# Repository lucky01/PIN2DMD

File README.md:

# PIN2DMD - a color LED dotmatrix controller for virtual and real pinballs

With the PIN2DMD project you get a full color LED DMD controller 
for real and virtual pinball machines.
The project was started by Lucky1 and shortly after that joined by Steve45 
as co-author. Version 1.X is free for DIY private NON COMMERCIAL use and released under 
a Creative Commons Attribution-NonCommercial- ShareAlike 4.0 International License.

http://creativecommons.org/licenses/by-nc-sa/4.0/

Due to copyright violations through commercial sales of our software the authors were forced to
change the project to allow access to the source code for contributors only with version 2.0.
Also a activation key which is bound to the hardware was introduced.
More Information how to obtain a key can be found in chapter 3 here https://pin2dmd.com/installation/ 

The latest binary can be found here 
https://github.com/lucky01/PIN2DMD/raw/master/firmware/latest/

Sorry for inconvinience, but is seems that the hunt for quick money eats the brain of the hunter.

More information can be found on https://pin2dmd.com/

It currently supports:

- WPC/WPC95 real pinball input
- Stern SAM real pinball input
- Stern Whitestar real pinball input
- Stern Spike real pinball input
- DataEast/Sega real pinball input
- Gottlieb real pinball input
- Capcom real pinball input
- AlvinG real pinball input
- Spooky real pinball input (with full color support from herg for AMH http://ledocd.com/amh_color/)
- Inder / SPinball real pinball input
- Sleic / Petaco real pinball input
- HomePin real pinball input
- Sega 192x64 using 64x64 1/32scan P2 Panels
- DataEast 128x16 real pinball input
- Mission Pinball Factory and P-ROC USB input
- Visual Pinball / PinMame USB input
- Future Pinball with DMD interceptor DLL
- Unit3d Pinball
- Ultra DMD support (Stephen)
- PinballX / XDMD support (Tom Speirs)
- Pinball fx2 support using dmdext from Freezy
- The Pinball Arcade support using dmdext from Freezy and NoEx
- Pinball Browser / SmartDMD color switching for full color Stern ROMS
- Frame colorization with PIN2DMD Editor by Steve for all pinball machines
- WCID Windows automated driver installation

The components cost approximately 120$
Here is a list of what you need:
 
#1. The Panels
The panels we use are sold for video walls and advertising signs. There are many 
sizes of panels available with different spacing between the LEDs. The ones 
that fit best into a pinball have 2.5mm spacing (also referred to as P2.5), 
which results in a 128×32 display of 320×76.8mm. This can be mounted into an 
existing DMD/speaker panel from a pinball cabinet. Currently the only place 
to buy these panels is from AliExpress. search for "RGB LED 64x64 p2.5 1/16" or 
"RGB LED 64x64 p2.5 1/16". You don´t find 128×32 panels, but you can buy two 
64×32 or one 64x64 panel which consists of two 64x32 panels which can be removed 
from the frame and connect side-by-side. Make sure that you end up with 2 x 1/16 
scan panels since these are the only one currently supported by PIN2DMD. 
The good thing is that they are seamless.

#2. The Controller

#2.1 The STM32 Nucleo board with PIN2DMD Shield or EVO boards

The panels use a 16 pin Hub75 interface to be connected to the next panel or to a 
controller. We use standard STM32 development boards like the Nucleo144-F429ZI or NUCLEO-F439ZI
which are available from multiple sources for about $20 or custom EVO boards.
The proceesor is based on a ARM Cortex processor architecture which is needed 
for the rapid bit-shifting of data to control the panels. We write the program in C/C++. 
The software is uploaded to the controller through USB port.
To connect the displays to the controller there is a HUB75 connector, which 
basically just connects the pins to the 16-pin ribbon cable that drives the displays. 
The board also has a 14pin connector which is used as input to get the data from a real machine. 
PCB layout examples can be found in the hardware directory. 

#3. The Power Supply
The RGB LED displays require 5vdc for power and if you want to run them
with full brightness they need a lot of current. A 10A power should be enough.
You need to connect that power supply up to both panels. The controller can 
either be supplied by USB or by an external 5V power source
 
#4. The Firmware
Installation is done using ST-Link interface

1) Download and install ST Link Utility: http://www.st.com/web/en/catalog/tools/PF258168
2) The latest binary can be found here https://github.com/lucky01/PIN2DMD/raw/master/firmware/latest/
3) Connect the STM32 board to the PC using a mini-USB cable (not the smaller microUSB cable). The board will light up and you should an STM32 STLink USB device connected in the Windows notification tray
4) Flash firmware: Target -> Program 
Choose PIN2DMD.BIN file from firmware/latest latest folder.

#5. The pin2dmd.exe tool
The tool is used to configure the controller und upload needed data for the pinball
used. It can either run in commandline mode or in GUI mode.

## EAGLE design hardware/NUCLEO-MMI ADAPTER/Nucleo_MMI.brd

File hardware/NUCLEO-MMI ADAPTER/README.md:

# PIN2DMD Nucleo MMI adapter

The files are provided as is for unmodified production use only.
Any modification without written approval is forbidden.

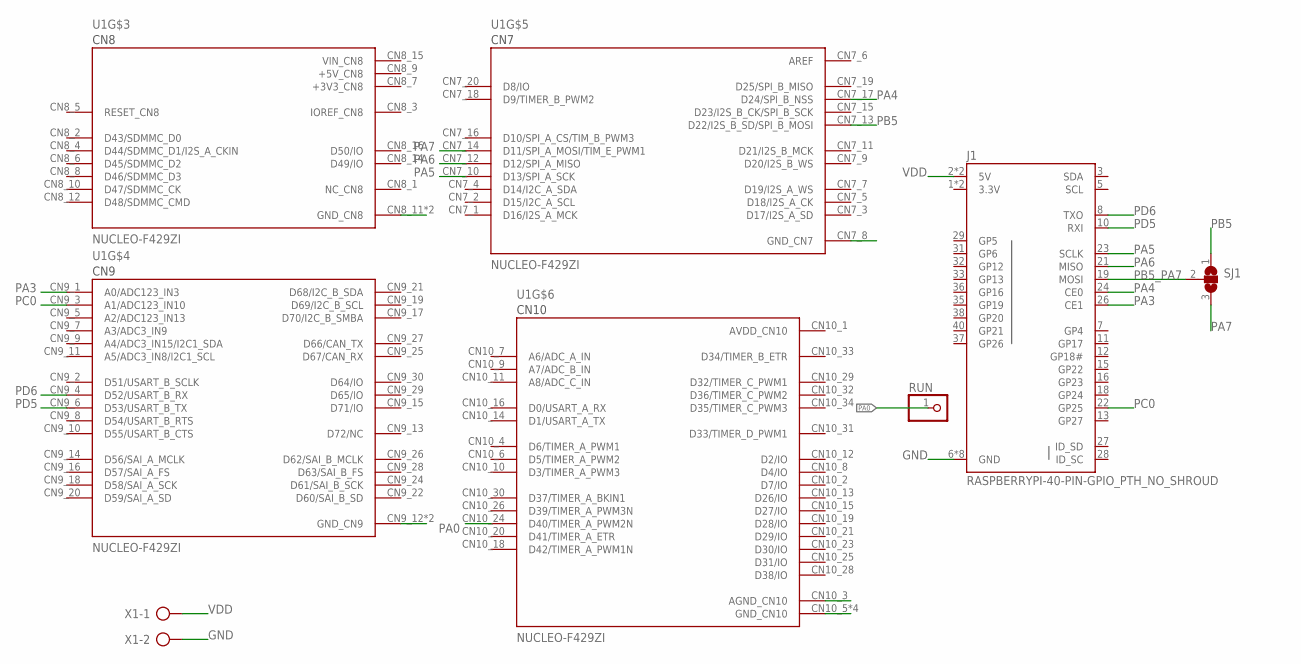
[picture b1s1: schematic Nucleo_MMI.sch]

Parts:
J1: RASPBERRYPI-40-PIN-GPIO_PTH_NO_SHROUD; 2X20
RUN: PINHD-1X1; 1X01
SJ1: SJ2W; SJ_2
U1: NUCLEO-F429ZI; MODULE_NUCLEO-F429ZI
X1: AK500/2-H

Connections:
3.3V: J1.1 (3.3V), J1.17 (3.3V)
+3V3_CN8: U1.CN8_7 (+3V3_CN8)
+5V_CN8: U1.CN8_9 (+5V_CN8)
AREF: U1.CN7_6 (AREF)
AVDD_CN10: U1.CN10_1 (AVDD_CN10)
GND: J1.6 (GND), J1.9 (GND), J1.14 (GND), J1.20 (GND), J1.25 (GND), J1.30 (GND), J1.34 (GND), J1.39 (GND), U1.CN7_8 (GND_CN7), U1.CN8_11 (GND_CN8), U1.CN8_13 (GND_CN8), U1.CN9_12 (GND_CN9), U1.CN9_23 (GND_CN9), U1.CN10_3 (AGND_CN10), U1.CN10_5 (GND_CN10), U1.CN10_17 (GND_CN10), U1.CN10_22 (GND_CN10), U1.CN10_27 (GND_CN10), X1.2
PA0: RUN.1, U1.CN10_24 (D40/TIMER_A_PWM2N)
PA3: J1.26 (CE1), U1.CN9_1 (A0/ADC123_IN3)
PA4: J1.24 (CE0), U1.CN7_17 (D24/SPI_B_NSS)
PA5: J1.23 (SCLK), U1.CN7_10 (D13/SPI_A_SCK)
PA6: J1.21 (MISO), U1.CN7_12 (D12/SPI_A_MISO)
PA7: SJ1.3, U1.CN7_14 (D11/SPI_A_MOSI/TIM_E_PWM1)
PB5: SJ1.1, U1.CN7_13 (D22/I2S_B_SD/SPI_B_MOSI)
PB5_PA7: J1.19 (MOSI), SJ1.2
PC0: J1.22 (GP25), U1.CN9_3 (A1/ADC123_IN10)
PD5: J1.10 (RXI), U1.CN9_6 (D53/USART_B_TX)
PD6: J1.8 (TXO), U1.CN9_4 (D52/USART_B_RX)
VDD: J1.2 (5V), J1.4 (5V), X1.1
VIN_CN8: U1.CN8_15 (VIN_CN8)

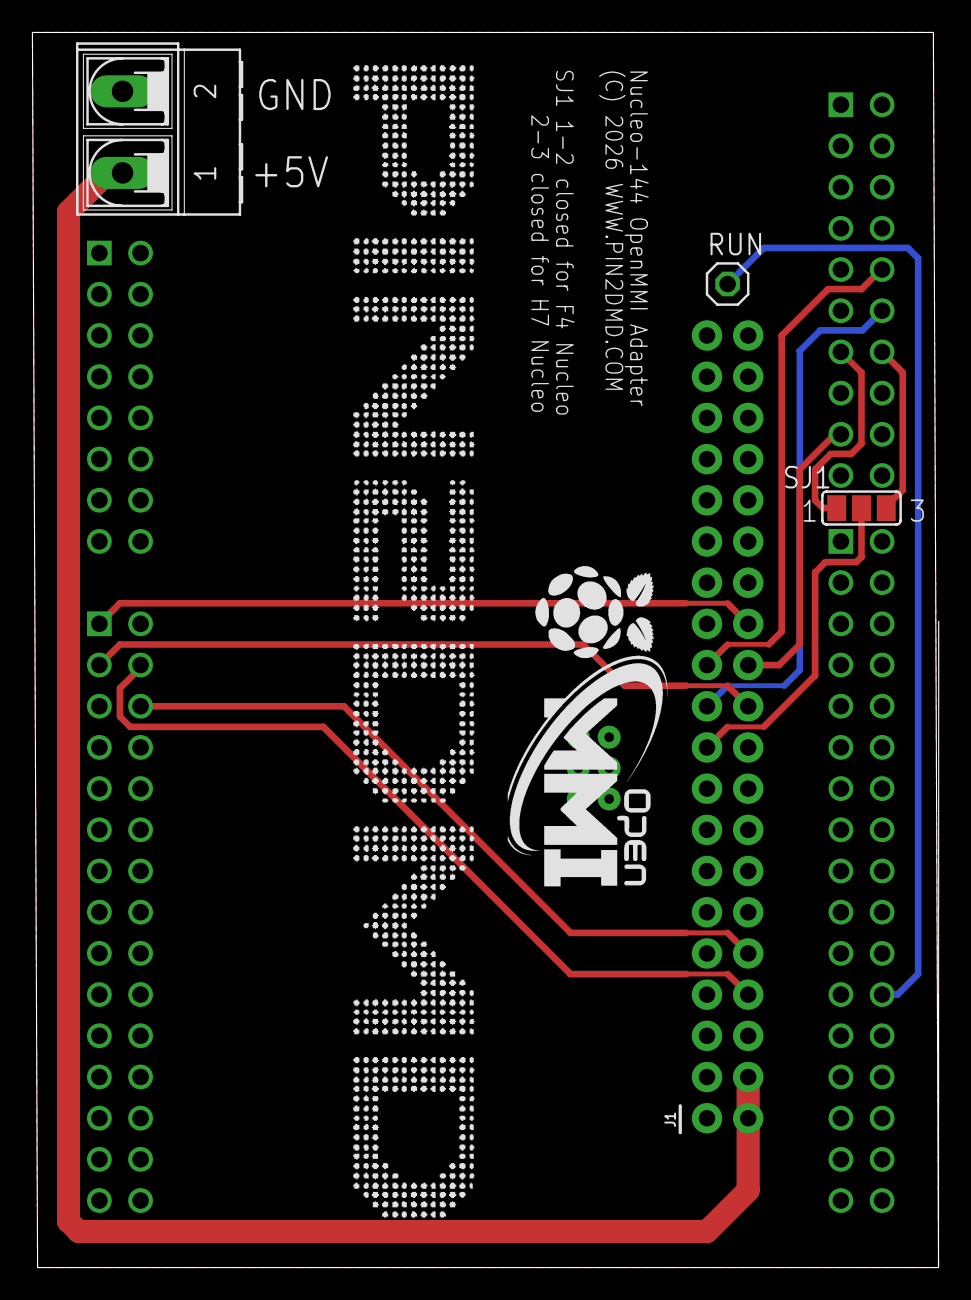
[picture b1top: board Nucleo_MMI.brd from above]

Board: 2 copper layers, 55.9 x 76.2 mm, 5 parts (1 on the bottom side), 14 nets.

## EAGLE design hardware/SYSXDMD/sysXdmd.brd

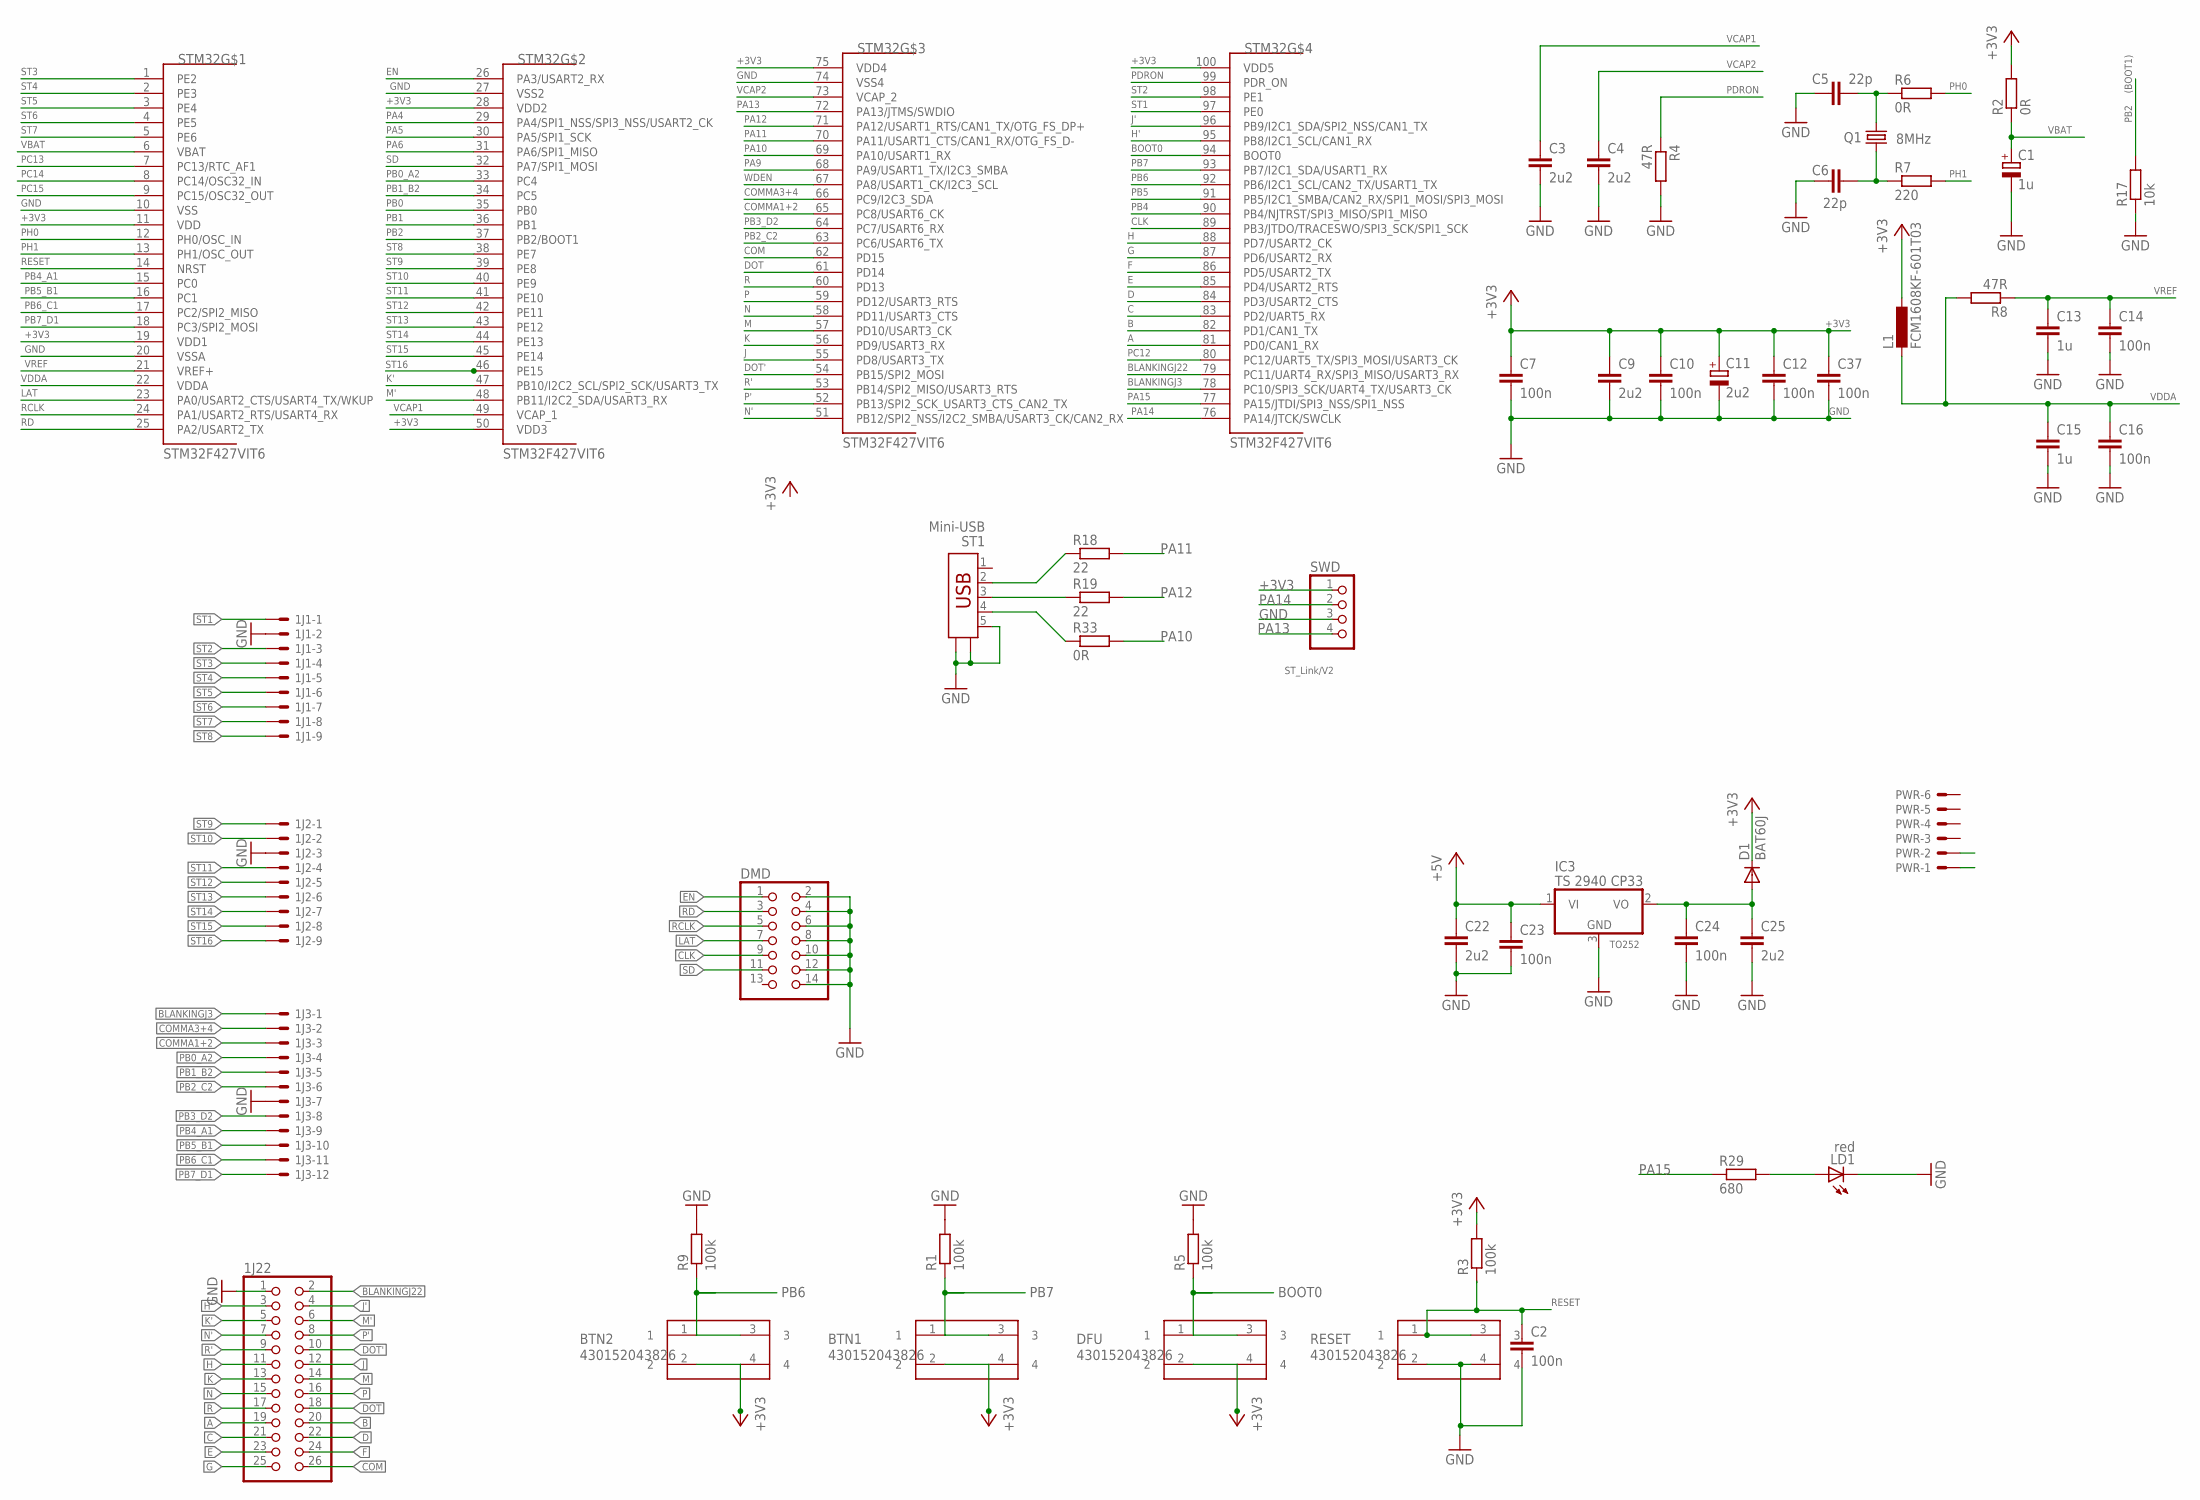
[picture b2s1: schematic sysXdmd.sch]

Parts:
1J1, 1J2: KK-156-9
1J3: KK-156-12
1J22: PINHD-2X13; 2X13
BTN1, BTN2: 430152043826
C1: 1u; CT3528
C2, C7, C10, C12, C14, C16, C23, C24, C37: 100n; C0805
C3, C4: 2u2; C0805
C5, C6: 22p; C0805
C9, C22, C25: 2u2; C1206
C11: 2u2; CT3528
C13, C15: 1u; C1206
D1: BAT60J; SOD323-W
DFU: 430152043826
DMD: PINHD-2X7; 2X07
IC3: TS 2940 CP33; TO252
L1: FCM1608KF-601T03; L0603
LD1: red; CHIP-LED0805
PWR: KK-156-6
Q1: 8MHz; HC49UP
R1, R3, R5, R9: 100k; R0805
R2, R6, R33: 0R; R0805
R4, R8: 47R; R0805
R7: 220; R0805
R17: 10k; R0805
R18, R19: 22; R0805
R29: 680; R0805
RESET: 430152043826
ST1: Mini-USB; USBMINI
STM32: STM32F427VIT6; LQFP100
SWD: PINHD-1X4; 1X04

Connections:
+3V3: BTN1.2, BTN1.4, BTN2.2, BTN2.4, C7.1, C9.1, C10.1, C11.+, C12.1, C37.1, D1.C, DFU.2, DFU.4, L1.1, R2.2, R3.2, STM32.11 (VDD), STM32.19 (VDD1), STM32.28 (VDD2), STM32.50 (VDD3), STM32.75 (VDD4), STM32.100 (VDD5), SWD.1
+5V: C22.1, C23.1, IC3.1 (VI), PWR.1
A: 1J22.19, STM32.81 (PD0/CAN1_RX)
B: 1J22.20, STM32.82 (PD1/CAN1_TX)
BLANKINGJ3: 1J3.1, STM32.78 (PC10/SPI3_SCK/UART4_TX/USART3_CK)
BLANKINGJ22: 1J22.2, STM32.79 (PC11/UART4_RX/SPI3_MISO/USART3_RX)
BOOT0: DFU.1, DFU.3, R5.1, STM32.94 (BOOT0)
C: 1J22.21, STM32.83 (PD2/UART5_RX)
CLK: DMD.9, STM32.89 (PB3/JTDO/TRACESWO/SPI3_SCK/SPI1_SCK)
COM: 1J22.26, STM32.62 (PD15)
COMMA1+2: 1J3.3, STM32.65 (PC8/USART6_CK)
COMMA3+4: 1J3.2, STM32.66 (PC9/I2C3_SDA)
D: 1J22.22, STM32.84 (PD3/USART2_CTS)
DOT: 1J22.18, STM32.61 (PD14)
DOT': 1J22.10, STM32.54 (PB15/SPI2_MOSI)
E: 1J22.23, STM32.85 (PD4/USART2_RTS)
EN: DMD.1, STM32.26 (PA3/USART2_RX)
F: 1J22.24, STM32.86 (PD5/USART2_TX)
G: 1J22.25, STM32.87 (PD6/USART2_RX)
GND: 1J1.2, 1J2.3, 1J3.7, 1J22.1, C1.-, C2.2, C3.2, C4.2, C5.2, C6.2, C7.2, C9.2, C10.2, C11.-, C12.2, C13.2, C14.2, C15.2, C16.2, C22.2, C23.2, C24.2, C25.2, C37.2, DMD.2, DMD.4, DMD.6, DMD.8, DMD.10, DMD.12, DMD.14, IC3.3 (GND), LD1.C, PWR.2, R1.2, R4.2, R5.2, R9.2, R17.1, RESET.2, RESET.4, ST1.5, ST1.N1, ST1.N2, STM32.10 (VSS), STM32.20 (VSSA), STM32.27 (VSS2), STM32.74 (VSS4), SWD.3
H: 1J22.11, STM32.88 (PD7/USART2_CK)
H': 1J22.3, STM32.95 (PB8/I2C1_SCL/CAN1_RX)
J: 1J22.12, STM32.55 (PD8/USART3_TX)
J': 1J22.4, STM32.96 (PB9/I2C1_SDA/SPI2_NSS/CAN1_TX)
K: 1J22.13, STM32.56 (PD9/USART3_RX)
K': 1J22.5, STM32.47 (PB10/I2C2_SCL/SPI2_SCK/USART3_TX)
LAT: DMD.7, STM32.23 (PA0/USART2_CTS/USART4_TX/WKUP)
M: 1J22.14, STM32.57 (PD10/USART3_CK)
M': 1J22.6, STM32.48 (PB11/I2C2_SDA/USART3_RX)
N: 1J22.15, STM32.58 (PD11/USART3_CTS)
unnamed: C5.1, Q1.2, R6.1
unnamed: C6.1, Q1.1, R7.1
unnamed: C24.1, C25.1, D1.A, IC3.2 (VO)
unnamed: LD1.A, R29.2
unnamed: R33.1, ST1.4
unnamed: R19.1, ST1.3
unnamed: R18.1, ST1.2
N': 1J22.7, STM32.51 (PB12/SPI2_NSS/I2C2_SMBA/USART3_CK/CAN2_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)
P: 1J22.16, STM32.59 (PD12/USART3_RTS)
P': 1J22.8, STM32.52 (PB13/SPI2_SCK_USART3_CTS_CAN2_TX)
PA4: STM32.29 (PA4/SPI1_NSS/SPI3_NSS/USART2_CK)
PA5: STM32.30 (PA5/SPI1_SCK)
PA6: STM32.31 (PA6/SPI1_MISO)
PA9: STM32.68 (PA9/USART1_TX/I2C3_SMBA)
PA10: R33.2, STM32.69 (PA10/USART1_RX)
PA11: R18.2, STM32.70 (PA11/USART1_CTS/CAN1_RX/OTG_FS_D-)
PA12: R19.2, STM32.71 (PA12/USART1_RTS/CAN1_TX/OTG_FS_DP+)
PA13: STM32.72 (PA13/JTMS/SWDIO), SWD.4
PA14: STM32.76 (PA14/JTCK/SWCLK), SWD.2
PA15: R29.1, STM32.77 (PA15/JTDI/SPI3_NSS/SPI1_NSS)
PB0: STM32.35 (PB0)
PB0_A2: 1J3.4, STM32.33 (PC4)
PB1: STM32.36 (PB1)
PB1_B2: 1J3.5, STM32.34 (PC5)
PB2: R17.2, STM32.37 (PB2/BOOT1)
PB2_C2: 1J3.6, STM32.63 (PC6/USART6_TX)
PB3_D2: 1J3.8, STM32.64 (PC7/USART6_RX)
PB4: STM32.90 (PB4/NJTRST/SPI3_MISO/SPI1_MISO)
PB4_A1: 1J3.9, STM32.15 (PC0)
PB5: STM32.91 (PB5/I2C1_SMBA/CAN2_RX/SPI1_MOSI/SPI3_MO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)
PB5_B1: 1J3.10, STM32.16 (PC1)
PB6: BTN2.1, BTN2.3, R9.1, STM32.92 (PB6/I2C1_SCL/CAN2_TX/USART1_TX)
PB6_C1: 1J3.11, STM32.17 (PC2/SPI2_MISO)
PB7: BTN1.1, BTN1.3, R1.1, STM32.93 (PB7/I2C1_SDA/USART1_RX)
PB7_D1: 1J3.12, STM32.18 (PC3/SPI2_MOSI)
PC12: STM32.80 (PC12/UART5_TX/SPI3_MOSI/USART3_CK)
PC13: STM32.7 (PC13/RTC_AF1)
PC14: STM32.8 (PC14/OSC32_IN)
PC15: STM32.9 (PC15/OSC32_OUT)
PDRON: R4.1, STM32.99 (PDR_ON)
PH0: R6.2, STM32.12 (PH0/OSC_IN)
PH1: R7.2, STM32.13 (PH1/OSC_OUT)
R: 1J22.17, STM32.60 (PD13)
R': 1J22.9, STM32.53 (PB14/SPI2_MISO/USART3_RTS)
RCLK: DMD.5, STM32.24 (PA1/USART2_RTS/USART4_RX)
RD: DMD.3, STM32.25 (PA2/USART2_TX)
RESET: C2.1, R3.1, RESET.1, RESET.3, STM32.14 (NRST)
SD: DMD.11, STM32.32 (PA7/SPI1_MOSI)
ST1: 1J1.1, STM32.97 (PE0)
ST2: 1J1.3, STM32.98 (PE1)
ST3: 1J1.4, STM32.1 (PE2)
ST4: 1J1.5, STM32.2 (PE3)
ST5: 1J1.6, STM32.3 (PE4)
ST6: 1J1.7, STM32.4 (PE5)
ST7: 1J1.8, STM32.5 (PE6)
ST8: 1J1.9, STM32.38 (PE7)
ST9: 1J2.1, STM32.39 (PE8)
ST10: 1J2.2, STM32.40 (PE9)
ST11: 1J2.4, STM32.41 (PE10)
ST12: 1J2.5, STM32.42 (PE11)
ST13: 1J2.6, STM32.43 (PE12)
ST14: 1J2.7, STM32.44 (PE13)
ST15: 1J2.8, STM32.45 (PE14)
ST16: 1J2.9, STM32.46 (PE15)
VBAT: C1.+, R2.1, STM32.6 (VBAT)
VCAP1: C3.1, STM32.49 (VCAP_1)
VCAP2: C4.1, STM32.73 (VCAP_2)
VDDA: C15.1, C16.1, L1.2, R8.2, STM32.22 (VDDA)
VREF: C13.1, C14.1, R8.1, STM32.21 (VREF+)
WDEN: STM32.67 (PA8/USART1_CK/I2C3_SCL)

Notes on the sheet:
TO252
(BOOT1)
ST_Link/V2

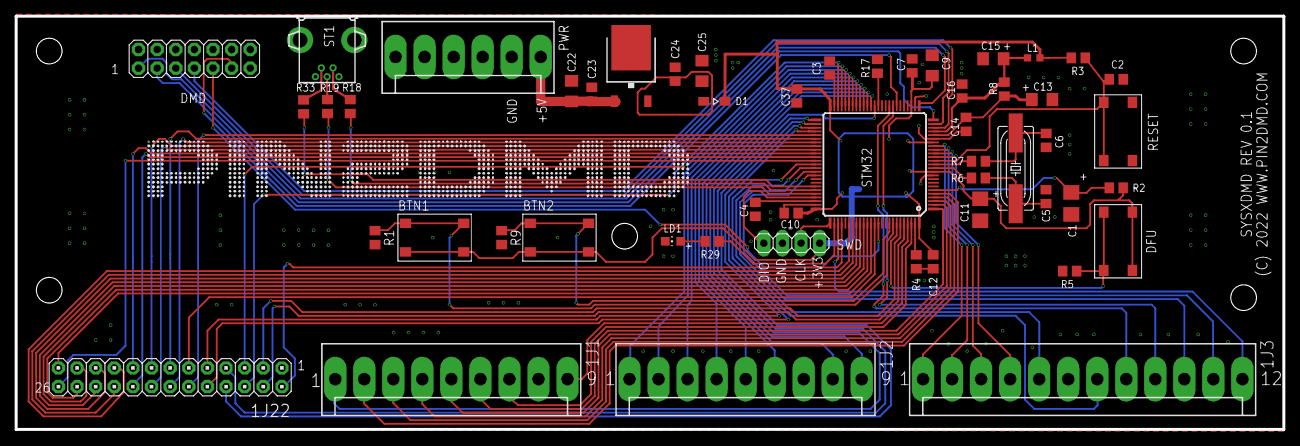
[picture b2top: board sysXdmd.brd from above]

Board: 2 copper layers, 172.9 x 56.4 mm, 52 parts (0 on the bottom side), 87 nets.

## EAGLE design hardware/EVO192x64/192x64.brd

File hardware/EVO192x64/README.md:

# PIN2DMD EVO192x64

The files are provided as is for unmodified production use only.
Any modification without written approval is forbidden.

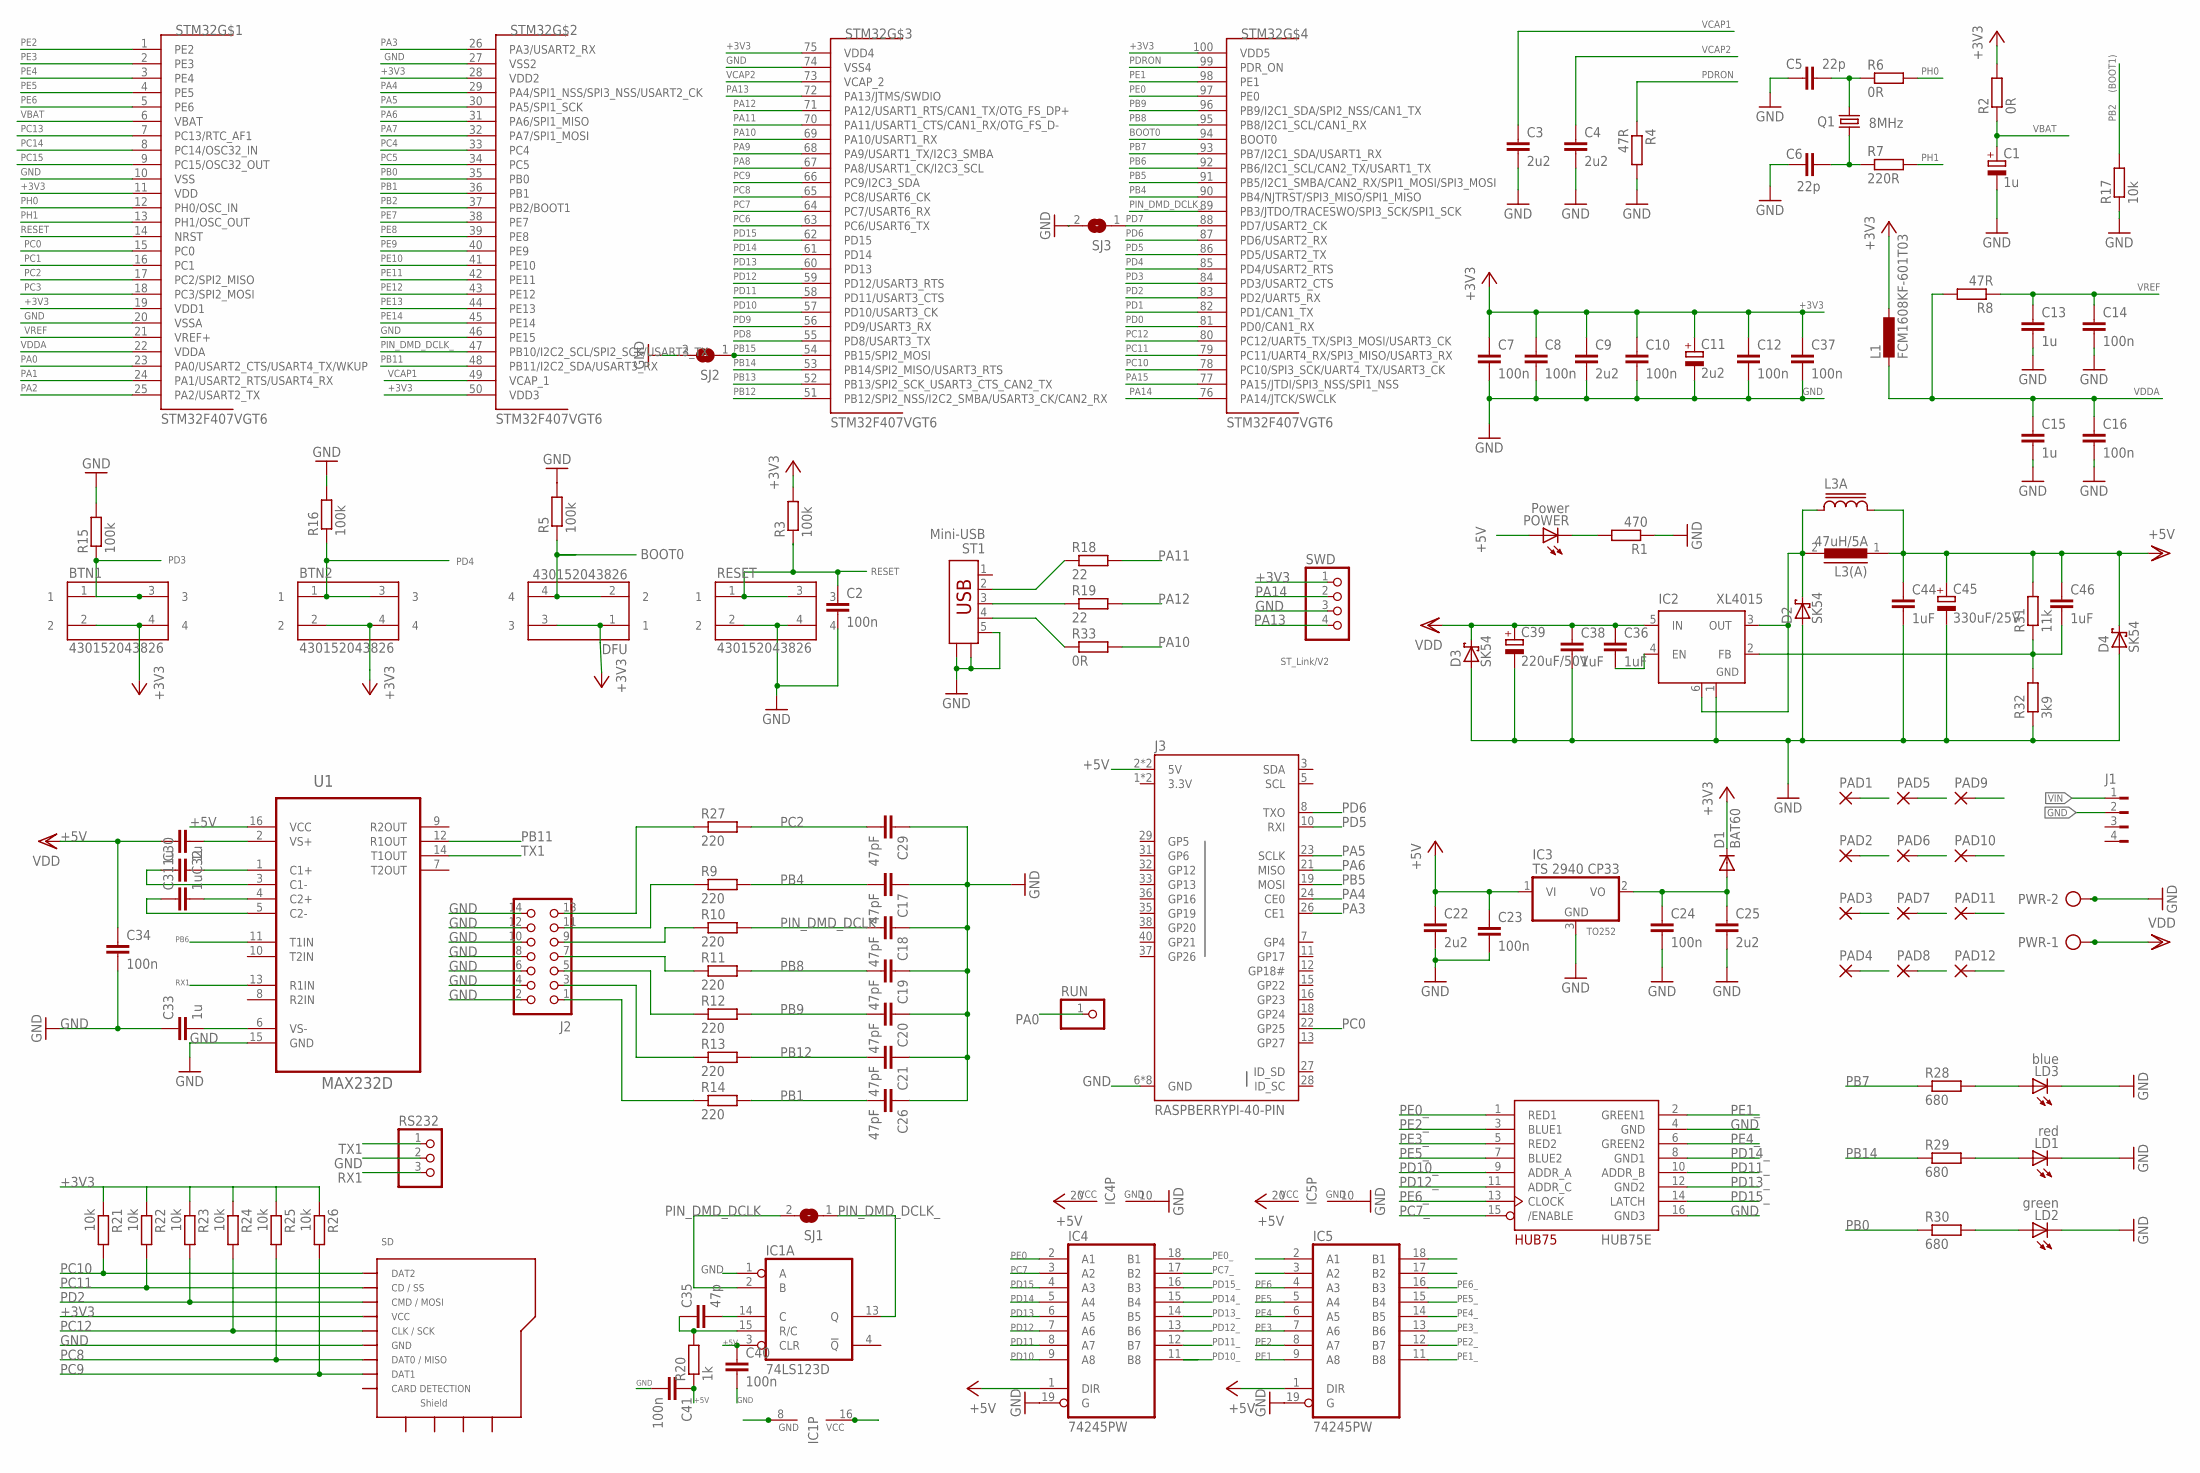
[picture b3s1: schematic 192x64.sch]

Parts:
BTN1, BTN2: 430152043826
C1: 1u; CT3528
C2, C7, C8, C10, C12, C14, C16, C23, C24, C34, C37, C40, C41: 100n; C0805
C3, C4: 2u2; C0805
C5, C6: 22p; C0805
C9, C22, C25: 2u2; C1206
C11: 2u2; CT3528
C13, C15: 1u; C1206
C17, C18, C19, C20, C21, C26, C29: 47pF; C0805
C30, C31, C32, C33: 1u; C0805
C35: 47p; C0805
C36, C38, C44, C46: 1uF; C1206
C39: 220uF/50V; PANASONIC_G
C45: 330uF/25V; PANASONIC_G
D1: BAT60; SOD323-W
D2, D3, D4: SK54; SMB
DFU: 430152043826
HUB75E: RGB; 2X08-IDC
IC1: 74LS123D; SO16
IC2: XL4015; TO263-5
IC3: TS 2940 CP33; TO252
IC4, IC5: 74245PW; TSSOP20
J1: FLOPPY-4
J2: CON_HEADER_2X07-PTH-SHROUDED; PINSHRD_PTH_2X07
J3: RASPBERRYPI-40-PIN; 2X20
L1: FCM1608KF-601T03; L2012C
L3(A): 47uH/5A; ED16
L3A: SRR1206
LD1: red; CHIP-LED0805
LD2: green; CHIP-LED0805
LD3: blue; CHIP-LED0805
PAD1, PAD2, PAD3, PAD4, PAD5, PAD6, PAD7, PAD8, PAD9, PAD10, PAD11, PAD12: SMD5; SMD2,54-5,08
POWER: Power; CHIPLED_0805
PWR: AK500/2-H
Q1: 8MHz; HC49UP
R1: 470; R0805
R2, R6, R33: 0R; R0805
R3, R5, R15, R16: 100k; R0805
R4, R8: 47R; R0805
R7: 220R; R0805
R9, R10, R11, R12, R13, R14, R27: 220; R0805
R17, R21, R22, R23, R24, R25, R26: 10k; R0805
R18, R19: 22; R0805
R20: 1k; R0805
R28, R29, R30: 680; R0805
R31: 11k; R1206
R32: 3k9; R1206
RESET: 430152043826
RS232: PINHD-1X3; 1X03
RUN: PINHD-1X1; 1X01
SD: MICROSD_CARD_POLLIN; MR**-AP*03**
SJ1, SJ2, SJ3: SJ
ST1: Mini-USB; USBMINI
STM32: STM32F407VGT6; LQFP100
SWD: PINHD-1X4; 1X04
U1: MAX232D; SOIC127P600X175-16N

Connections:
3.3V: J3.1 (3.3V), J3.17 (3.3V)
+3V3: BTN1.2, BTN1.4, BTN2.2, BTN2.4, C7.1, C8.1, C9.1, C10.1, C11.+, C12.1, C37.1, D1.C, DFU.1, DFU.3, L1.1, R2.2, R3.2, R21.1, R22.1, R23.1, R24.1, R25.1, R26.1, SD.VCC, STM32.11 (VDD), STM32.19 (VDD1), STM32.28 (VDD2), STM32.50 (VDD3), STM32.75 (VDD4), STM32.100 (VDD5), SWD.1
+5V: C22.1, C23.1, C32.2, C34.1, C40.1, C41.1, C44.1, C45.+, C46.1, D4.C, IC1.3 (CLR), IC1.16 (VCC), IC3.1 (VI), IC4.1 (DIR), IC4.20 (VCC), IC5.1 (DIR), IC5.20 (VCC), J3.2 (5V), J3.4 (5V), L3(A).1, L3A.2, PAD1.1, PAD2.1, PAD5.1, PAD6.1, PAD9.1, PAD10.1, POWER.A, R20.1, R31.2, U1.16 (VCC)
BOOT0: DFU.2, DFU.4, R5.1, STM32.94 (BOOT0)
GND: C1.-, C2.2, C3.2, C4.2, C5.2, C6.2, C7.2, C8.2, C9.2, C10.2, C11.-, C12.2, C13.2, C14.2, C15.2, C16.2, C17.1, C18.1, C19.1, C20.1, C21.1, C22.2, C23.2, C24.2, C25.2, C26.1, C29.1, C33.1, C34.2, C37.2, C38.2, C39.-, C40.2, C41.2, C44.2, C45.-, D2.A, D3.A, D4.A, HUB75E.4 (GND), HUB75E.16 (GND3), IC1.1 (A), IC1.8 (GND), IC2.1 (GND), IC3.3 (GND), IC4.10 (GND), IC4.19 (G), IC5.2 (A1), IC5.3 (A2), IC5.10 (GND), IC5.19 (G), J1.2, J2.2, J2.4, J2.6, J2.8, J2.10, J2.12, J2.14, J3.6 (GND), J3.9 (GND), J3.14 (GND), J3.20 (GND), J3.25 (GND), J3.30 (GND), J3.34 (GND), J3.39 (GND), LD1.C, LD2.C, LD3.C, PAD3.1, PAD4.1, PAD7.1, PAD8.1, PAD11.1, PAD12.1, PWR.2, R1.1, R4.2, R5.2, R15.2, R16.2, R17.1, R32.1, RESET.2, RESET.4, RS232.2, SD.GND, SJ2.2, SJ3.2, ST1.5, ST1.N1, ST1.N2, STM32.10 (VSS), STM32.20 (VSSA), STM32.27 (VSS2), STM32.46 (PE15), STM32.74 (VSS4), SWD.3, U1.15 (GND)
unnamed: C5.1, Q1.2, R6.1
unnamed: C6.1, Q1.1, R7.1
unnamed: POWER.C, R1.2
unnamed: J2.13, R27.1
unnamed: J2.11, R9.1
unnamed: J2.9, R10.1
unnamed: J2.7, R11.1
unnamed: J2.5, R12.1
unnamed: J2.3, R13.1
unnamed: C35.1, IC1.15 (R/C), R20.2
unnamed: J2.1, R14.1
unnamed: C24.1, C25.1, D1.A, IC3.2 (VO)
unnamed: C30.2, U1.1 (C1+)
unnamed: C30.1, U1.3 (C1-)
unnamed: C31.2, U1.4 (C2+)
unnamed: C31.1, U1.5 (C2-)
unnamed: C33.2, U1.6 (VS-)
unnamed: C32.1, U1.2 (VS+)
unnamed: LD1.A, R29.2
unnamed: D2.C, IC2.3 (OUT), IC2.6 (TAB), L3(A).2, L3A.1
unnamed: C46.2, IC2.2 (FB), R31.1, R32.2
unnamed: C35.2, IC1.14 (C)
unnamed: LD3.A, R28.2
unnamed: C36.2, IC2.4 (EN)
unnamed: R33.1, ST1.4
unnamed: LD2.A, R30.2
unnamed: R19.1, ST1.3
unnamed: R18.1, ST1.2
PA0: RUN.1, STM32.23 (PA0/USART2_CTS/USART4_TX/WKUP)
PA1: STM32.24 (PA1/USART2_RTS/USART4_RX)
PA2: STM32.25 (PA2/USART2_TX)
PA3: J3.26 (CE1), STM32.26 (PA3/USART2_RX)
PA4: J3.24 (CE0), STM32.29 (PA4/SPI1_NSS/SPI3_NSS/USART2_CK)
PA5: J3.23 (SCLK), STM32.30 (PA5/SPI1_SCK)
PA6: J3.21 (MISO), STM32.31 (PA6/SPI1_MISO)
PA7: STM32.32 (PA7/SPI1_MOSI)
PA8: STM32.67 (PA8/USART1_CK/I2C3_SCL)
PA9: STM32.68 (PA9/USART1_TX/I2C3_SMBA)
PA10: R33.2, STM32.69 (PA10/USART1_RX)
PA11: R18.2, STM32.70 (PA11/USART1_CTS/CAN1_RX/OTG_FS_D-)
PA12: R19.2, STM32.71 (PA12/USART1_RTS/CAN1_TX/OTG_FS_DP+)
PA13: STM32.72 (PA13/JTMS/SWDIO), SWD.4
PA14: STM32.76 (PA14/JTCK/SWCLK), SWD.2
PA15: STM32.77 (PA15/JTDI/SPI3_NSS/SPI1_NSS)
PB0: R30.1, STM32.35 (PB0)
PB1: C26.2, R14.2, STM32.36 (PB1)
PB2: R17.2, STM32.37 (PB2/BOOT1)
PB4: C17.2, R9.2, STM32.90 (PB4/NJTRST/SPI3_MISO/SPI1_MISO)
PB5: J3.19 (MOSI), STM32.91 (PB5/I2C1_SMBA/CAN2_RX/SPI1_MOSI/SPI3_MO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)
PB6: STM32.92 (PB6/I2C1_SCL/CAN2_TX/USART1_TX), U1.11 (T1IN)
PB7: R28.1, STM32.93 (PB7/I2C1_SDA/USART1_RX)
PB8: C19.2, R11.2, STM32.95 (PB8/I2C1_SCL/CAN1_RX)
PB9: C20.2, R12.2, STM32.96 (PB9/I2C1_SDA/SPI2_NSS/CAN1_TX)
PB11: STM32.48 (PB11/I2C2_SDA/USART3_RX), U1.12 (R1OUT)
PB12: C21.2, R13.2, STM32.51 (PB12/SPI2_NSS/I2C2_SMBA/USART3_CK/CAN2_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)
PB13: STM32.52 (PB13/SPI2_SCK_USART3_CTS_CAN2_TX)
PB14: R29.1, STM32.53 (PB14/SPI2_MISO/USART3_RTS)
PB15: SJ2.1, STM32.54 (PB15/SPI2_MOSI)
PC0: J3.22 (GP25), STM32.15 (PC0)
PC1: STM32.16 (PC1)
PC2: C29.2, R27.2, STM32.17 (PC2/SPI2_MISO)
PC3: STM32.18 (PC3/SPI2_MOSI)
PC4: STM32.33 (PC4)
PC5: STM32.34 (PC5)
PC6: STM32.63 (PC6/USART6_TX)
PC7: IC4.3 (A2), STM32.64 (PC7/USART6_RX)
PC7_: HUB75E.15 (/ENABLE), IC4.17 (B2)
PC8: R25.2, SD.DAT0 (DAT0/MISO), STM32.65 (PC8/USART6_CK)
PC9: R26.2, SD.DAT1, STM32.66 (PC9/I2C3_SDA)
PC10: R21.2, SD.DAT2, STM32.78 (PC10/SPI3_SCK/UART4_TX/USART3_CK)
PC11: R22.2, SD.DAT3/CS (CD/SS), STM32.79 (PC11/UART4_RX/SPI3_MISO/USART3_RX)
PC12: R24.2, SD.CLK (CLK/SCK), STM32.80 (PC12/UART5_TX/SPI3_MOSI/USART3_CK)
PC13: STM32.7 (PC13/RTC_AF1)
PC14: STM32.8 (PC14/OSC32_IN)
PC15: STM32.9 (PC15/OSC32_OUT)
PD0: STM32.81 (PD0/CAN1_RX)
PD1: STM32.82 (PD1/CAN1_TX)
PD2: R23.2, SD.CMD (CMD/MOSI), STM32.83 (PD2/UART5_RX)
PD3: BTN1.1, BTN1.3, R15.1, STM32.84 (PD3/USART2_CTS)
PD4: BTN2.1, BTN2.3, R16.1, STM32.85 (PD4/USART2_RTS)
PD5: J3.10 (RXI), STM32.86 (PD5/USART2_TX)
PD6: J3.8 (TXO), STM32.87 (PD6/USART2_RX)
PD7: SJ3.1, STM32.88 (PD7/USART2_CK)
PD8: STM32.55 (PD8/USART3_TX)
PD9: STM32.56 (PD9/USART3_RX)
PD10: IC4.9 (A8), STM32.57 (PD10/USART3_CK)
PD10_: HUB75E.9 (ADDR_A), IC4.11 (B8)
PD11: IC4.8 (A7), STM32.58 (PD11/USART3_CTS)
PD11_: HUB75E.10 (ADDR_B), IC4.12 (B7)
PD12: IC4.7 (A6), STM32.59 (PD12/USART3_RTS)
PD12_: HUB75E.11 (ADDR_C), IC4.13 (B6)
PD13: IC4.6 (A5), STM32.60 (PD13)
PD13_: HUB75E.12 (GND2), IC4.14 (B5)
PD14: IC4.5 (A4), STM32.61 (PD14)
PD14_: HUB75E.8 (GND1), IC4.15 (B4)
PD15: IC4.4 (A3), STM32.62 (PD15)
PD15_: HUB75E.14 (LATCH), IC4.16 (B3)
PDRON: R4.1, STM32.99 (PDR_ON)
PE0: IC4.2 (A1), STM32.97 (PE0)
PE0_: HUB75E.1 (RED1), IC4.18 (B1)
PE1: IC5.9 (A8), STM32.98 (PE1)
PE1_: HUB75E.2 (GREEN1), IC5.11 (B8)
PE2: IC5.8 (A7), STM32.1 (PE2)
PE2_: HUB75E.3 (BLUE1), IC5.12 (B7)
PE3: IC5.7 (A6), STM32.2 (PE3)
PE3_: HUB75E.5 (RED2), IC5.13 (B6)
PE4: IC5.6 (A5), STM32.3 (PE4)
PE4_: HUB75E.6 (GREEN2), IC5.14 (B5)
PE5: IC5.5 (A4), STM32.4 (PE5)
PE5_: HUB75E.7 (BLUE2), IC5.15 (B4)
PE6: IC5.4 (A3), STM32.5 (PE6)
PE6_: HUB75E.13 (CLOCK), IC5.16 (B3)
PE7: STM32.38 (PE7)
PE8: STM32.39 (PE8)
PE9: STM32.40 (PE9)
PE10: STM32.41 (PE10)
PE11: STM32.42 (PE11)
PE12: STM32.43 (PE12)
PE13: STM32.44 (PE13)
PE14: STM32.45 (PE14)
PH0: R6.2, STM32.12 (PH0/OSC_IN)
PH1: R7.2, STM32.13 (PH1/OSC_OUT)
PIN_DMD_DCLK: C18.2, IC1.2 (B), R10.2, SJ1.2
PIN_DMD_DCLK_: IC1.13 (Q), SJ1.1, STM32.47 (PB10/I2C2_SCL/SPI2_SCK/USART3_TX), STM32.89 (PB3/JTDO/TRACESWO/SPI3_SCK/SPI1_SCK)
RESET: C2.1, R3.1, RESET.1, RESET.3, STM32.14 (NRST)
RX1: RS232.3, U1.13 (R1IN)
TX1: RS232.1, U1.14 (T1OUT)
VBAT: C1.+, R2.1, STM32.6 (VBAT)
VCAP1: C3.1, STM32.49 (VCAP_1)
VCAP2: C4.1, STM32.73 (VCAP_2)
VDDA: C15.1, C16.1, L1.2, R8.2, STM32.22 (VDDA)
VIN: C36.1, C38.1, C39.+, D3.C, IC2.5 (IN), J1.1, PWR.1
VREF: C13.1, C14.1, R8.1, STM32.21 (VREF+)

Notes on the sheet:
TO252
(BOOT1)
ST_Link/V2

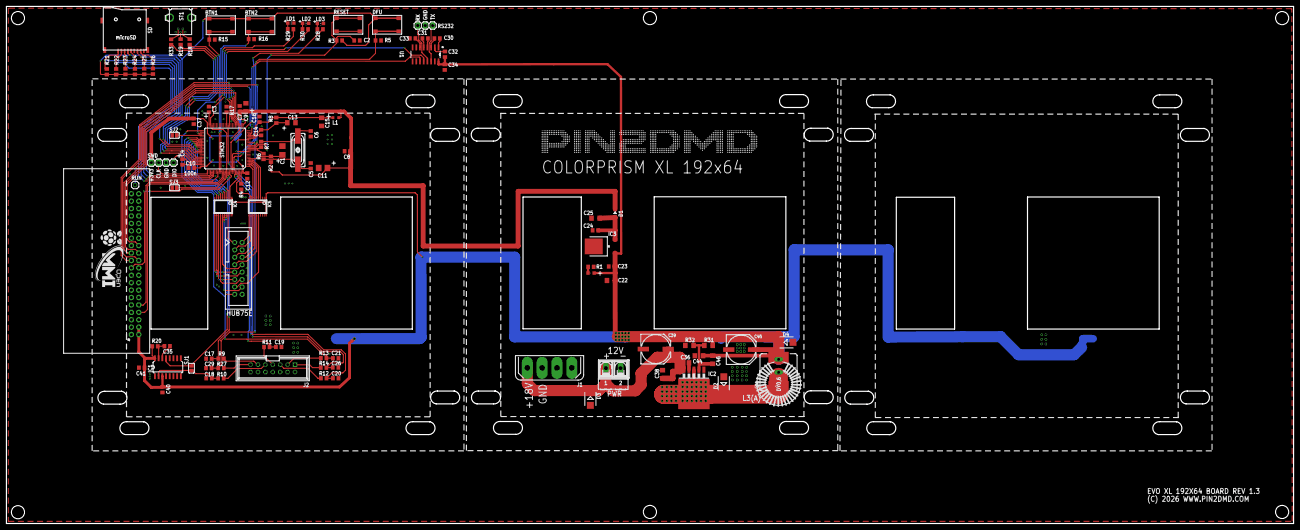
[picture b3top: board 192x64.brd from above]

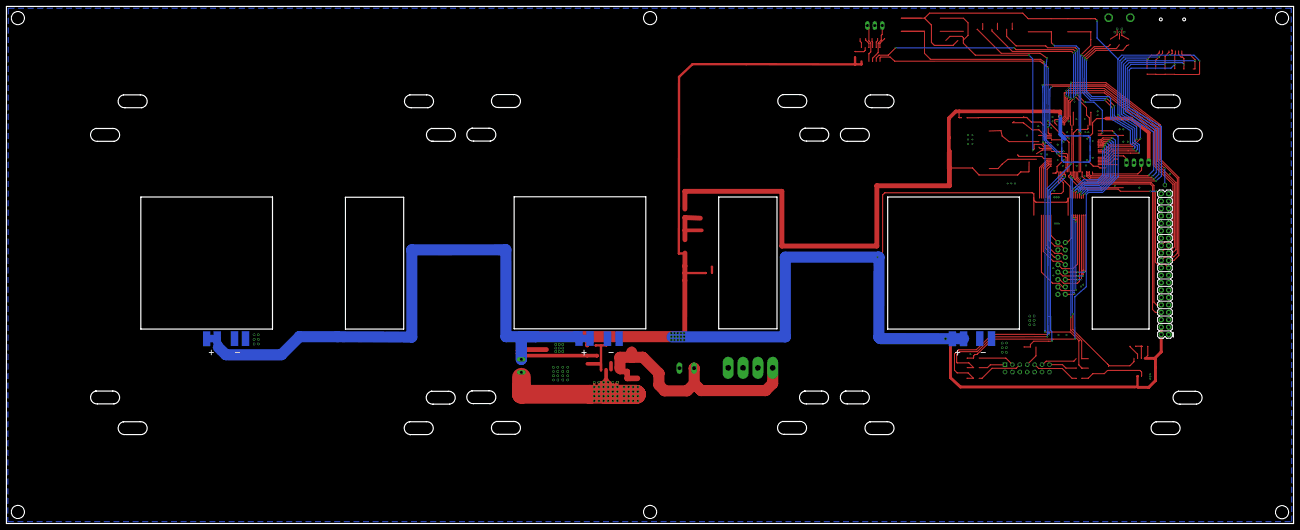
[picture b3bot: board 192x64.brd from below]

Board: 2 copper layers, 441.1 x 177.2 mm, 123 parts (13 on the bottom side), 111 nets.

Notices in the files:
hardware/DC-DC CONVERTER/PIN2DMD_PWR.brd:
(c) 2017 www.pin2dmd.com
hardware/EVO192x64/192x64.brd:
(C) 2026 WWW.PIN2DMD.COM
hardware/EVO256x64/EVO256x64.brd:
(C) 2025 WWW.PIN2DMD.COM
hardware/SYSXDMD/sysXdmd.brd:
(C) 2022 WWW.PIN2DMD.COM
hardware/V4 NUCLEO-144/chinese SD Reader/PIN2DMD_Nucleo144.brd:
(c) 2020 www.pin2dmd.com
parts and their libraries:
Wuerth_Elektronik_eiCan_05_Box_Header_ID: Copyright: Würth Elektronik
SparkFun-Connectors: Licensing: Creative Commons ShareAlike 4.0 International - https://creativecommons.org/licenses/by-sa/4.0
inductor-bourns: Copyright (C) 2008, Bob Starr
